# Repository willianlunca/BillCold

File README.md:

# Termokip
Repositório com arquivos relacionados ao hardware da versão 1.1

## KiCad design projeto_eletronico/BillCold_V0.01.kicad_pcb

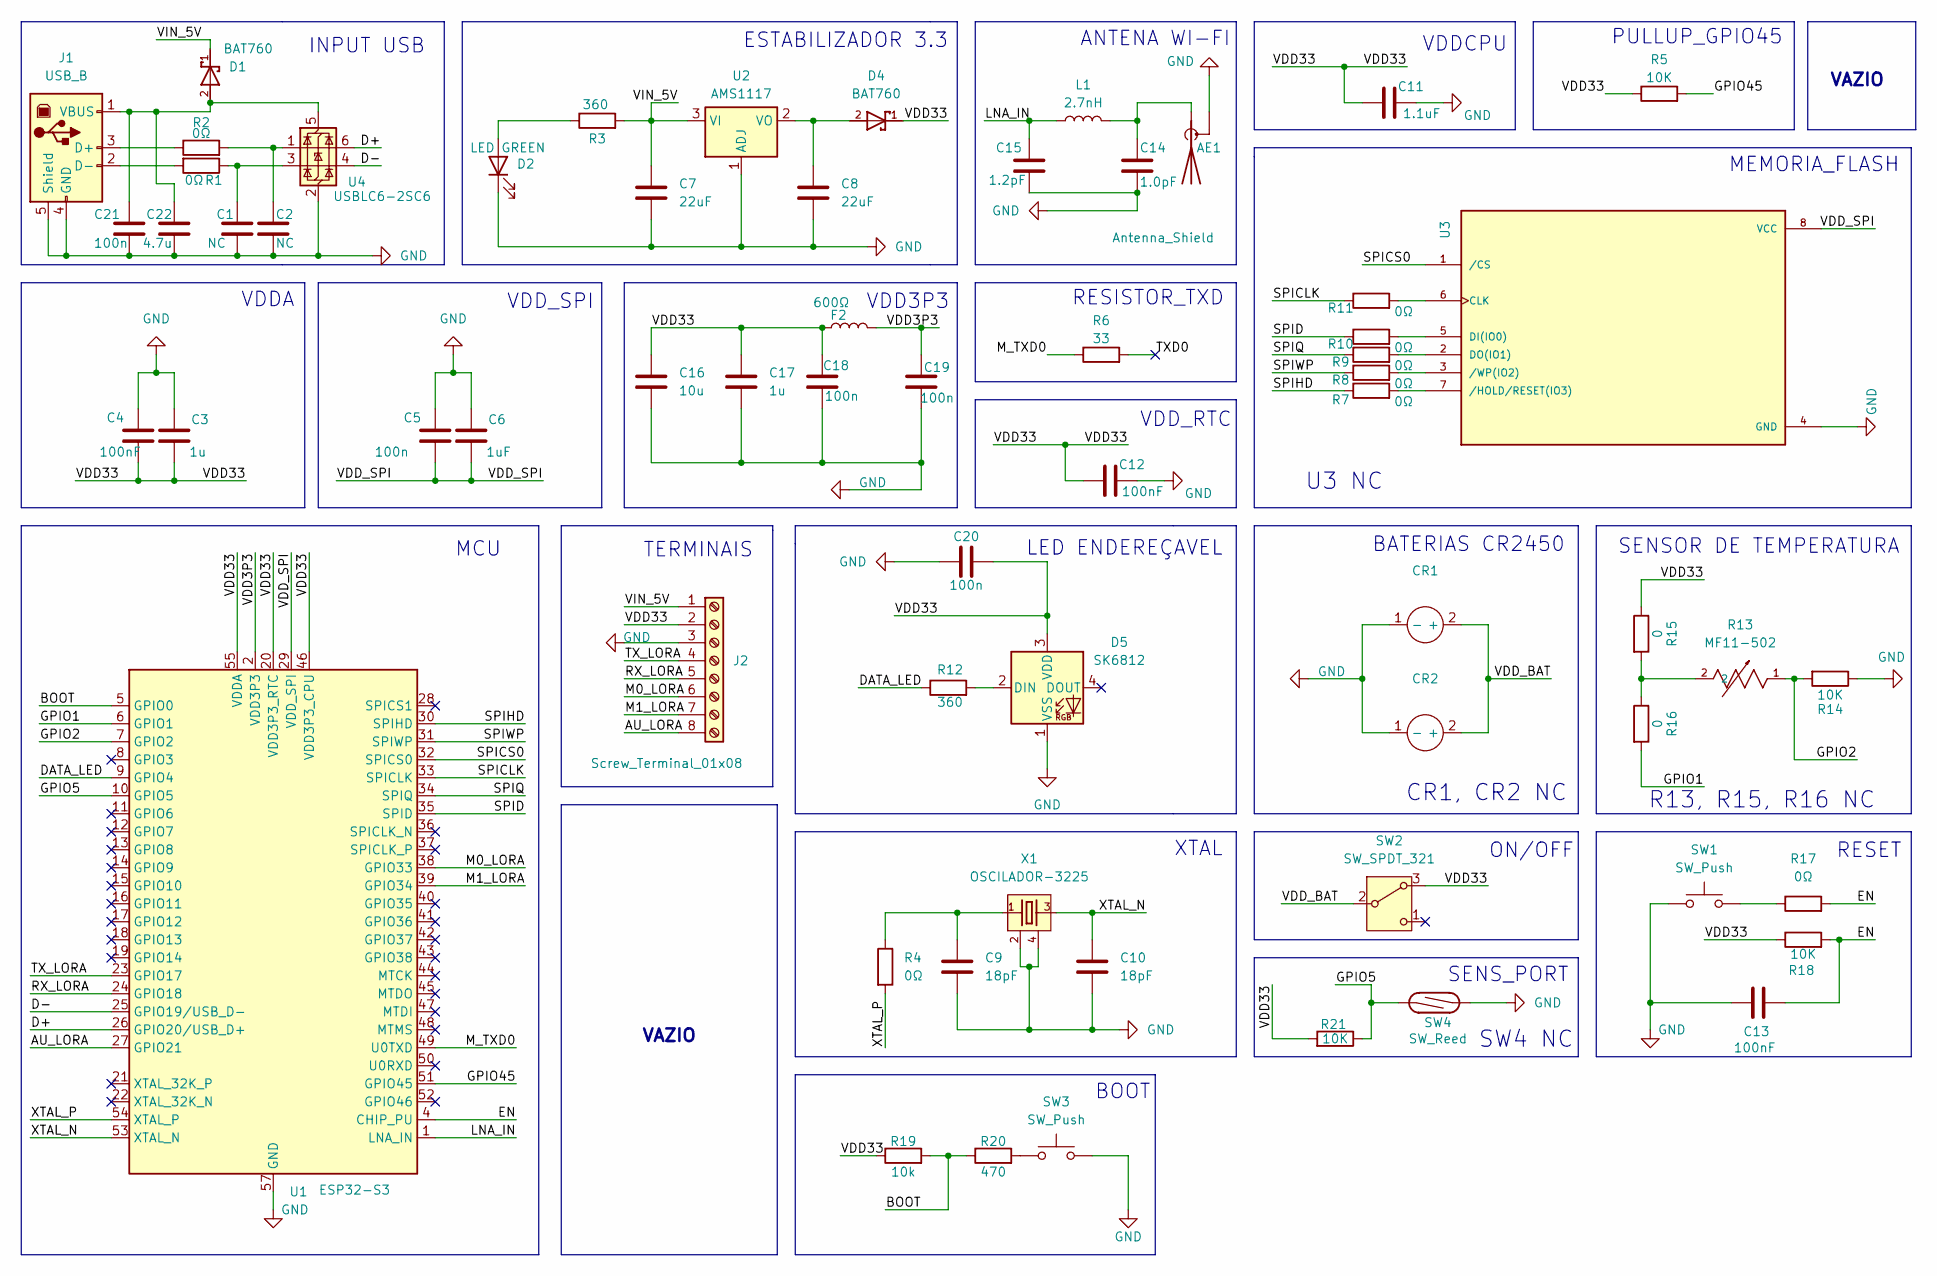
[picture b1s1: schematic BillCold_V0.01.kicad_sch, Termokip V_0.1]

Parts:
AE1: Antenna_Shield; Texas_SWRA117D_2.4GHz_Right
C1, C2: NC; C_0603_1608Metric
C3, C17: 1u; C_0603_1608Metric
C4, C12, C13: 100nF; C_0603_1608Metric
C5, C18, C19, C20, C21: 100n; C_0603_1608Metric
C6: 1uF; C_0603_1608Metric
C7, C8: 22uF; C_0603_1608Metric
C9, C10: 18pF; C_0603_1608Metric
C11: 1.1uF; C_0603_1608Metric
C14: 1.0pF; C_0603_1608Metric
C15: 1.2pF; C_0603_1608Metric
C16: 10u; C_0603_1608Metric
C22: 4.7u; C_0603_1608Metric
CR1, CR2: CR2450_SUPORT
D1, D4: BAT760; SOD323_F_
D2: LED GREEN; LED_1206_3216Metric
D5: SK6812; LED_WS2812B-Mini_PLCC4_3.5x3.5mm
F2: 600Ω; L_0805_2012Metric
J1: USB_B; CUI_UJ2-BV-1-TH
J2: Screw_Terminal_01x08; TerminalBlock_MaiXu_MX126-5.0-08P_1x08_P5.00mm
L1: 2.7nH; L_0805_2012Metric
R1, R2, R4, R7, R8, R9, R10, R11, R17: 0Ω; R_0603_1608Metric
R3, R12: 360; R_0603_1608Metric
R5, R14, R18, R21: 10K; R_0603_1608Metric
R6: 33; R_0603_1608Metric
R13: MF11-502; TRES_MF52-A_CTM; MANUFACTURER_PART_NUMBER MF52A1103F3380
R15, R16: 0; R_Axial_DIN0204_L3.6mm_D1.6mm_P5.08mm_Horizontal
R19: 10k; R_0603_1608Metric
R20: 470; R_0603_1608Metric
SW1, SW3: SW_Push; SW_Push_1P1T_NO_E-Switch_TL3301NxxxxxG
SW2: SW_SPDT_321; SW_SPDT_Shouhan_MSK12C02
SW4: SW_Reed; R_Axial_DIN0614_L14.3mm_D5.7mm_P20.32mm_Horizontal
U1: ESP32-S3; QFN-56-1EP_7x7mm_P0.4mm_EP4x4mm
U2: AMS1117; SOT-223-3_TabPin2
U3: W25Q128JVSIQ; SOIC127P790X216-8N; PARTREV I
U4: USBLC6-2SC6; SOT-23-6
X1: OSCILADOR-3225; TSX-3225

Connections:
/AU_LORA: J2.8, U1.27 (GPIO21)
/BOOT: R19.2, R20.1, U1.5 (GPIO0)
/D+: U1.26 (GPIO20/USB_D+), U4.6 (I/O1)
/D-: U1.25 (GPIO19/USB_D-), U4.4 (I/O2)
/DATA_LED: R12.1, U1.9 (GPIO4)
/EN: C13.2, R17.2, R18.2, U1.4 (CHIP_PU)
/GPIO1: R16.2, U1.6 (GPIO1)
/GPIO2: R13.1, R14.2, U1.7 (GPIO2)
/GPIO5: R21.1, SW4.2, U1.10 (GPIO5)
/GPIO45: R5.2, U1.51 (GPIO45)
/LNA_IN: C15.1, L1.1, U1.1 (LNA_IN)
/M0_LORA: J2.6, U1.38 (GPIO33)
/M1_LORA: J2.7, U1.39 (GPIO34)
/M_TXD0: R6.1, U1.49 (U0TXD)
/RX_LORA: J2.5, U1.24 (GPIO18)
/SPICLK: R11.1, U1.33 (SPICLK)
/SPICS0: U1.32 (SPICS0), U3.1 (/CS)
/SPID: R10.1, U1.35 (SPID)
/SPIHD: R7.1, U1.30 (SPIHD)
/SPIQ: R9.1, U1.34 (SPIQ)
/SPIWP: R8.1, U1.31 (SPIWP)
/TXD0: R6.2
/TX_LORA: J2.4, U1.23 (GPIO17)
/VDD3P3: C19.1, F2.2, U1.2 (VDD3P3), U1.3 (VDD3P3)
/VDD33: C3.2, C4.2, C11.1, C12.1, C16.1, C17.1, C18.1, C20.1, D4.1, D5.3 (VDD), F2.1, J2.2, R5.1, R15.1, R18.1, R19.1, R21.2, SW2.3 (A), U1.20 (VDD3P3_RTC), U1.46 (VDD3P3_CPU), U1.55 (VDDA), U1.56 (VDDA)
/VDD_BAT: CR1.2 (+), CR2.2 (+), SW2.2 (B)
/VDD_SPI: C5.2, C6.2, U1.29 (VDD_SPI), U3.8 (VCC)
/VIN_5V: C7.1, D1.1, J2.1, R3.2, U2.3 (VI)
/XTAL_N: C10.1, U1.53 (XTAL_N), X1.3
/XTAL_P: R4.2, U1.54 (XTAL_P)
GND: AE1.2 (Shield), C1.2, C2.2, C3.1, C4.1, C5.1, C6.1, C7.2, C8.2, C9.2, C10.2, C11.2, C12.2, C13.1, C14.2, C15.2, C16.2, C17.2, C18.2, C19.2, C20.2, C21.2, C22.2, CR1.1 (-), CR2.1 (-), D2.1 (K), D5.1 (VSS), J1.4 (GND), J1.5 (Shield), J2.3, R14.1, SW1.1, SW3.2, SW4.1, U1.57 (GND), U2.1 (ADJ), U3.4 (GND), U4.2 (GND), X1.2, X1.4
unnamed: AE1.1 (A), C14.1, L1.2
unnamed: C1.1, R1.1, U4.3 (I/O2)
unnamed: C2.1, R2.2, U4.1 (I/O1)
unnamed: C9.1, R4.1, X1.1
unnamed: D2.2 (A), R3.1
unnamed: D5.2 (DIN), R12.2
unnamed: J1.3 (D+), R2.1
unnamed: J1.2 (D-), R1.2
unnamed: C21.1, C22.1, D1.2, J1.1 (VBUS), U4.5 (VBUS)
unnamed: R13.2, R15.2, R16.1
unnamed: R17.1, SW1.2
unnamed: R20.2, SW3.1
unnamed: C8.1, D4.2, U2.2 (VO)
unnamed: R11.2, U3.6 (CLK)
unnamed: R10.2, U3.5 (DI(IO0))
unnamed: R9.2, U3.2 (DO(IO1))
unnamed: R7.2, U3.7 (/HOLD/RESET(IO3))
unnamed: R8.2, U3.3 (/WP(IO2))

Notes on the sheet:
U3 NC
RESET
ANTENA WI-FI
VDD3P3
VAZIO
SENSOR DE TEMPERATURA
VDD_SPI
BOOT
ON/OFF
R13, R15, R16 NC
LED ENDEREÇAVEL
TERMINAIS
RESISTOR_TXD
SENS_PORT
XTAL
VDD_RTC
MEMORIA_FLASH
INPUT USB
SW4 NC
ESTABILIZADOR 3.3
PULLUP_GPIO45
BATERIAS CR2450
VDDCPU
CR1, CR2 NC
VDDA
MCU

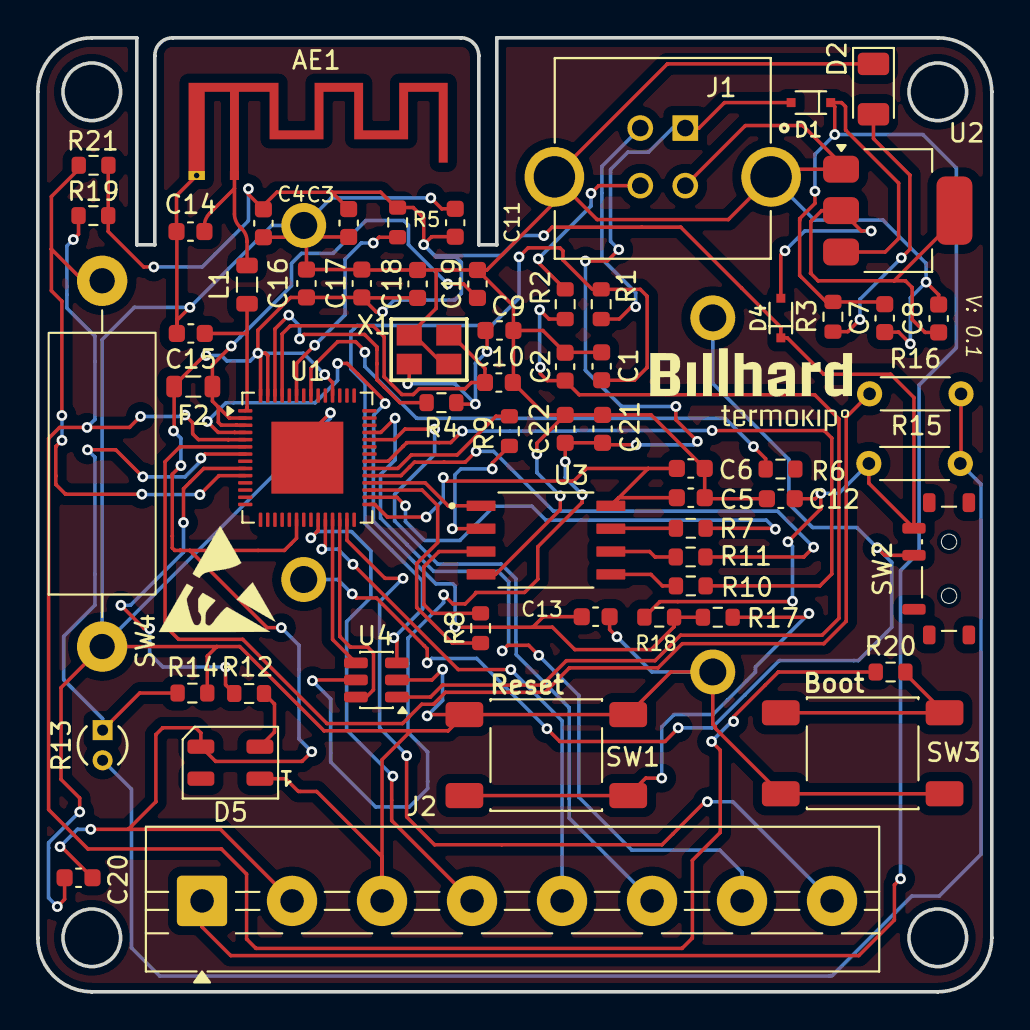
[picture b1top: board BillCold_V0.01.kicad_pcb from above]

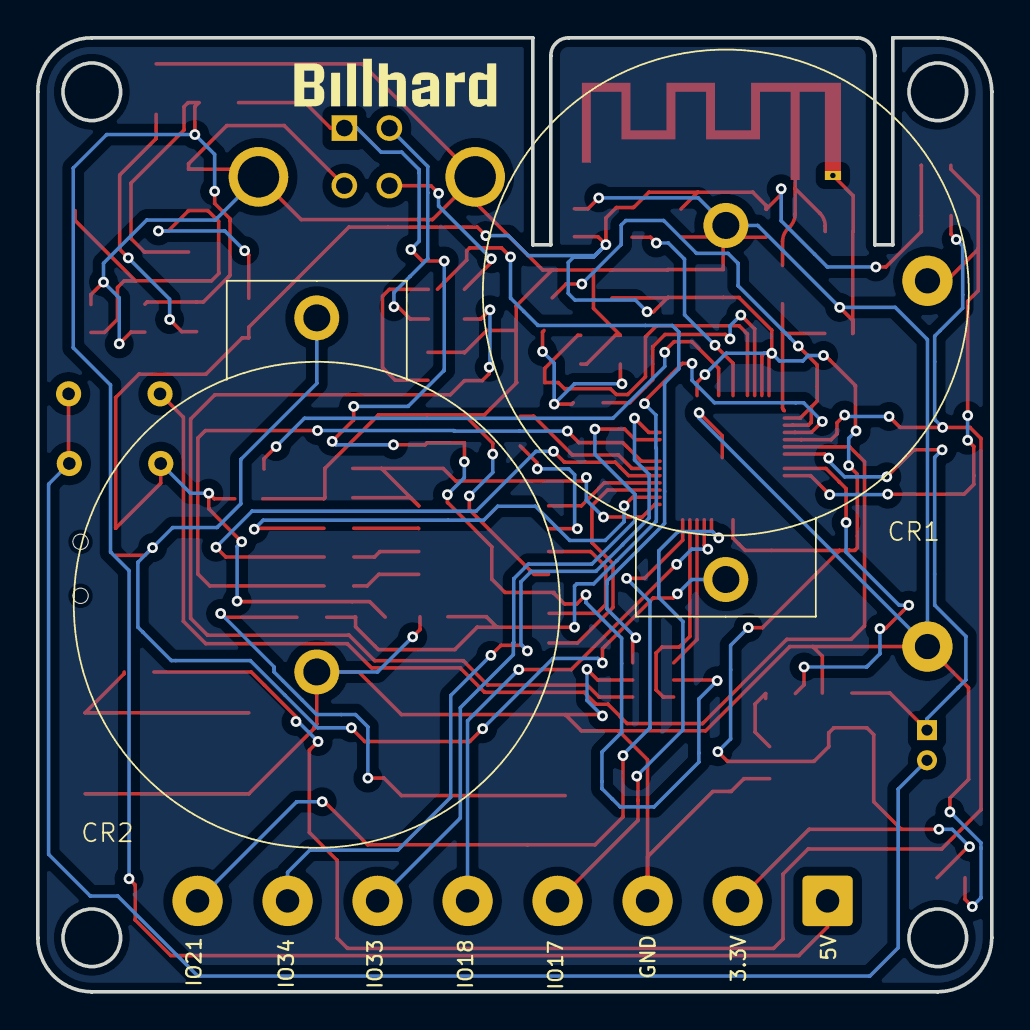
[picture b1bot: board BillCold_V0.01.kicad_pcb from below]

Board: 2 copper layers, 53.0 x 53.0 mm, 65 parts (3 on the bottom side), 48 nets.

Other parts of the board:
LV-01, LV-01#2: LOGO; Billhard_V01

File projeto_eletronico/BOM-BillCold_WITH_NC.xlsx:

Comment | Designator | Footprint | LCSC | Quantity
0Ω | R1,R10,R11,R17,R2,R4,R7,R8,R9 | R_0603_1608Metric | C95177 | 9
1.0pF | C14 | C_0603_1608Metric | C5137611 | 1
1.1uF | C11 | C_0603_1608Metric | C14663 | 1
1.2pF | C15 | C_0603_1608Metric | C2836766 | 1
100n | C18,C19,C20,C21 | C_0603_1608Metric | C125205 | 4
100n | C5 | C_0603_1608Metric | C14663 | 1
100nF | C12,C13 | C_0603_1608Metric | C14663 | 2
100nF | C4 | C_0603_1608Metric | C15849 | 1
10K | R14,R18,R21,R5 | R_0603_1608Metric | C98220 | 4
10k | R19 | R_0603_1608Metric | C98220 | 1
10u | C16 | C_0603_1608Metric | C19702 | 1
18pF | C10,C9 | C_0603_1608Metric | C1647 | 2
1u | C17 | C_0603_1608Metric | C15849 | 1
1u | C3 | C_0603_1608Metric | C96446 | 1
1uF | C6 | C_0603_1608Metric | C15849 | 1
2.7nH | L1 | L_0805_2012Metric | C578018 | 1
22uF | C7,C8 | C_0603_1608Metric | C86295 | 2
33 | R6 | R_0603_1608Metric | C2933227 | 1
360 | R3 | R_0603_1608Metric | C25194 | 1
360 | R12 | R_0603_1608Metric | C95177 | 1
4.7u | C22 | C_0603_1608Metric | C1705 | 1
470 | R20 | R_0603_1608Metric | C23179 | 1
600Ω | F2 | L_0805_2012Metric | C21519 | 1
AMS1117 | U2 | SOT-223-3_TabPin2 | C6186 | 1
BAT760 | D1,D4 | SOD323_F_ | C116158 | 2
ESP32-S3 | U1 | QFN-56-1EP_7x7mm_P0.4mm_EP4x4mm | C2913196 | 1
LED GREEN | D2 | LED_1206_3216Metric | C30584801 | 1
NC | C1,C2 | C_0603_1608Metric | C5137611 | 2
OSCILADOR-3225 | X1 | TSX-3225 | C521661 | 1
SW_Push | SW1,SW3 | SW_Push_1P1T_NO_E-Switch_TL3301NxxxxxG | C83206 | 2
SW_SPDT_321 | SW2 | SW_SPDT_Shouhan_MSK12C02 | C431540 | 1
USBLC6-2SC6 | U4 | SOT-23-6 | C7519 | 1
SK6812 | D5 | LED_WS2812B-Mini_PLCC4_3.5x3.5mm |  | 1
NC | SW4 | R_Axial_DIN0614_L14.3mm_D5.7mm_P20.32mm_Horizontal |  | 1
NC | R13 | TRES_MF52-A_CTM |  | 1
NC | R16 | R_Axial_DIN0204_L3.6mm_D1.6mm_P5.08mm_Horizontal |  | 1
USB_B | J1 | CUI_UJ2-BV-1-TH |  | 1
Antenna_Shield | AE1 | Texas_SWRA117D_2.4GHz_Right |  | 1
NC | U3 | SOIC127P790X216-8N |  | 1
Screw_Terminal_01x08 | J2 | TerminalBlock_MaiXu_MX126-5.0-08P_1x08_P5.00mm |  | 1
NC | R15 | R_Axial_DIN0204_L3.6mm_D1.6mm_P5.08mm_Horizontal |  | 1
NC | CR1 | CR2450_SUPORT |  | 1
NC | CR2 | CR2450_SUPORT |  | 1

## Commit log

2025-05-23 Enviando primeiros arquivos referente ao esquematico
2025-05-27 Finalizando o projeto do harware do mcu
2025-12-14 enviando componente de suporte de bateria
2025-12-14 Ignore .DS_Store
2025-12-16 Iniciando o roteamento das trilhas da PCB
2025-12-20 Projeto finalizado
2025-12-28 Alterando componentes smd 0603
2026-05-03 Conclusão do projeto
2026-05-03 Incindo configuração do projeto para versão 1.1
2026-05-03 Reunindo datasheets de componentes a ser utilizados dursnte o desenvolvimento
2026-05-04 Iniciando o desenvolvimento do esquematico reaproveitando partes já validadas na versão anterior.
2026-05-21 Removendo Arquivos do projeto versão anterior
2026-05-21 Iniciando o desenvolvimento do esquematico

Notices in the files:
parts and their libraries:
COPYRIGHT: Copyright (C) 2024 Ultra Librarian. All rights reserved.
